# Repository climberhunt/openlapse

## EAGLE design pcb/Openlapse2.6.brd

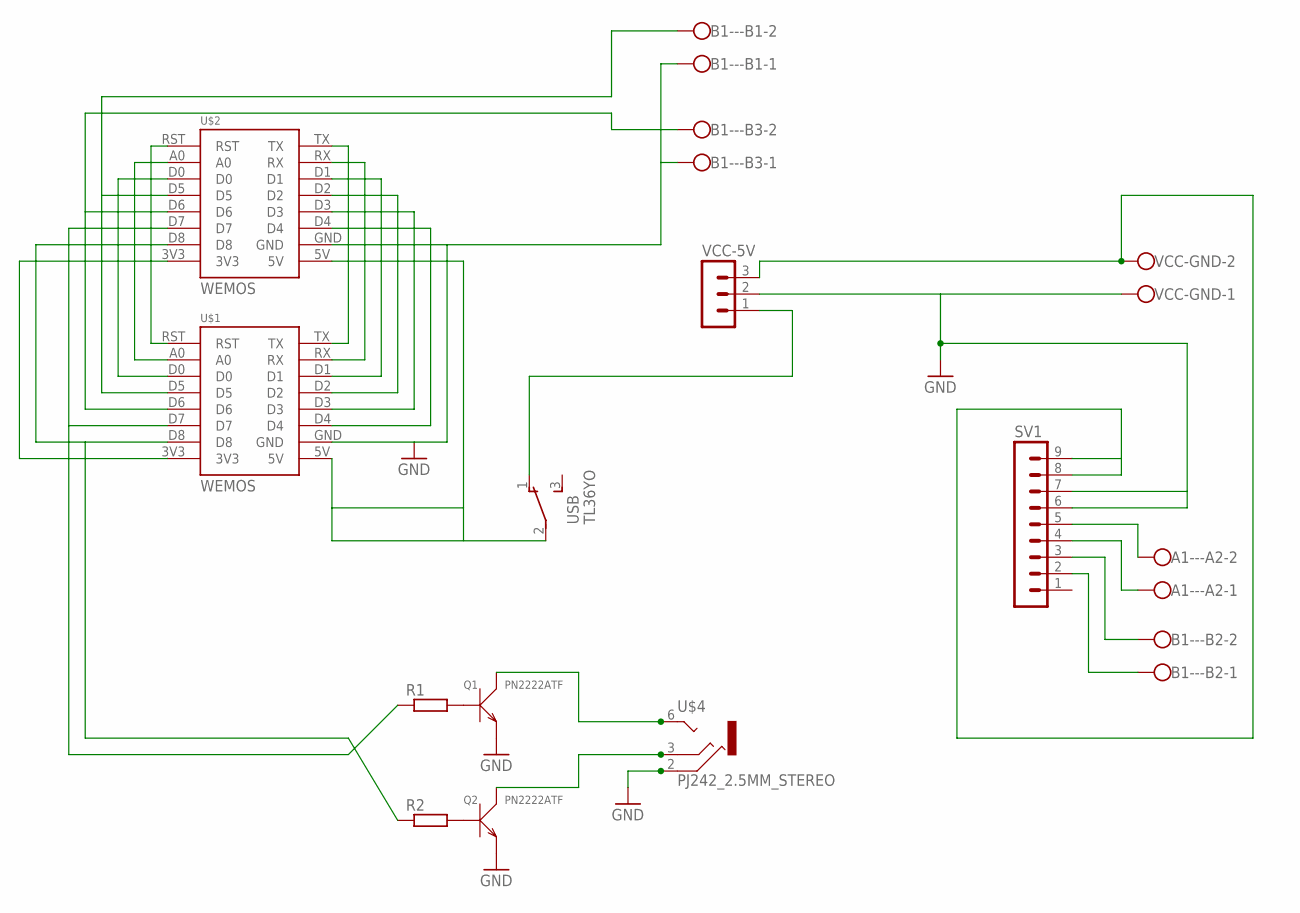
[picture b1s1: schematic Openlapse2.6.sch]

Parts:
A1---A2: W237-102
B1---B1, B1---B2, B1---B3: W237-102
Q1, Q2: PN2222ATF; TO-92
R1, R2: R0204/7; 0204/7
SV1: MA09-1
U$1, U$2: WEMOS
U$4: PJ242_2.5MM_STEREO
USB: TL36YO; TL3XYO
VCC-5V: MA03-1
VCC-GND: W237-102

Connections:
GND: B1---B1.1, B1---B3.1, Q1.1 (E), Q2.1 (E), SV1.6, SV1.7, U$1.GND, U$2.GND, U$4.2 (1), VCC-5V.2, VCC-GND.1
unnamed: SV1.8, SV1.9, VCC-5V.3, VCC-GND.2
unnamed: U$1.5V, U$2.5V, USB.2
unnamed: R2.1, U$1.D8, U$2.D8
unnamed: R1.1, U$1.D7, U$2.D7
unnamed: U$1.TX, U$2.TX
unnamed: U$1.RX, U$2.RX
unnamed: Q2.2 (B), R2.2
unnamed: Q1.2 (B), R1.2
unnamed: U$1.D1, U$2.D1
unnamed: U$1.D2, U$2.D2
unnamed: U$1.D3, U$2.D3
unnamed: U$1.D4, U$2.D4
unnamed: U$1.RST, U$2.RST
unnamed: U$1.A0, U$2.A0
unnamed: U$1.D0, U$2.D0
unnamed: B1---B1.2, U$1.D5, U$2.D5
unnamed: B1---B3.2, U$1.D6, U$2.D6
unnamed: Q1.3 (C), U$4.6 (2)
unnamed: USB.1 (O), VCC-5V.1
unnamed: U$1.3V3, U$2.3V3
unnamed: A1---A2.2, SV1.5
unnamed: A1---A2.1, SV1.4
unnamed: Q2.3 (C), U$4.3
unnamed: B1---B2.2, SV1.3
unnamed: B1---B2.1, SV1.2

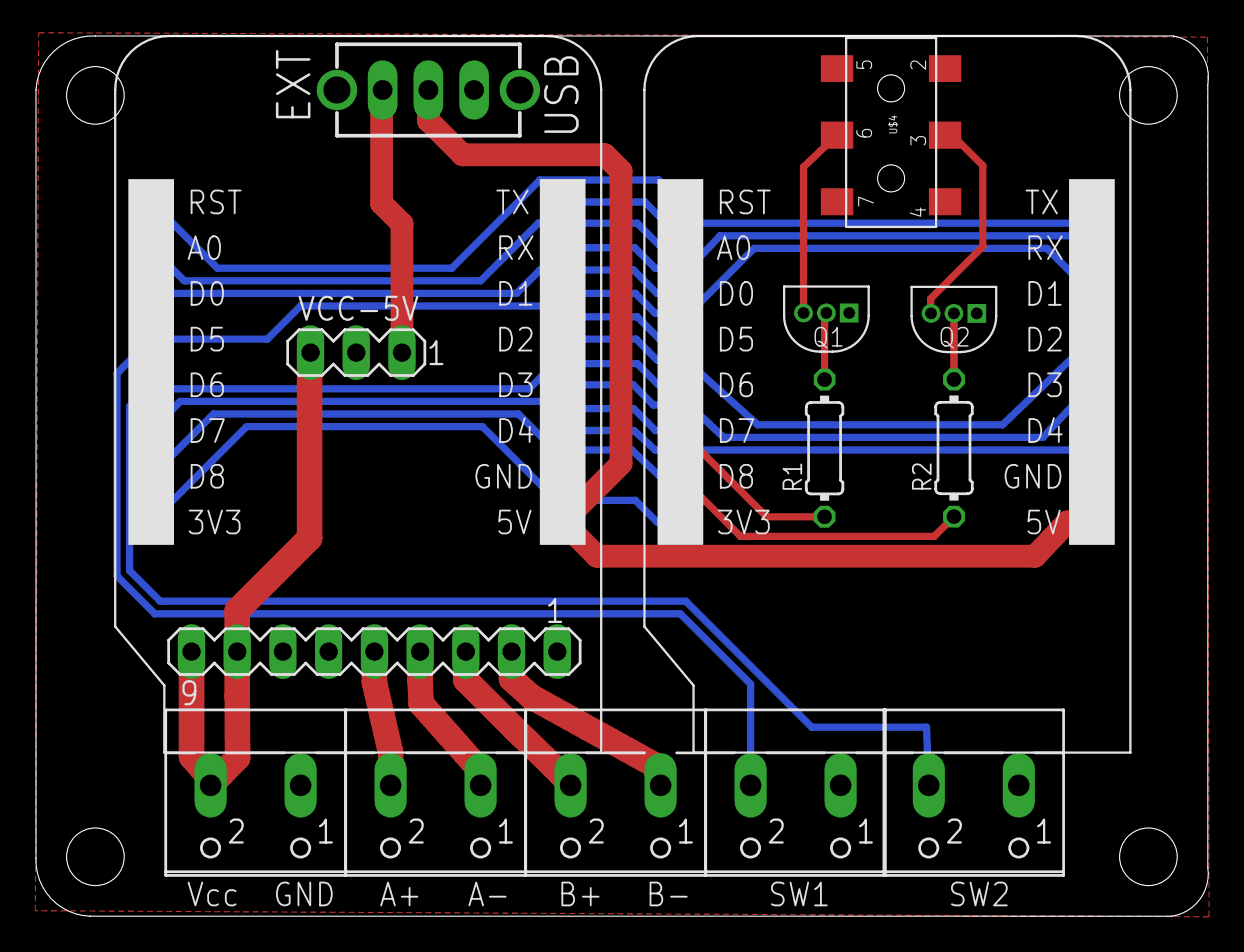
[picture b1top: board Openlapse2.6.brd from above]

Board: 2 copper layers, 65.1 x 48.9 mm, 15 parts (0 on the bottom side), 26 nets.

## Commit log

2017-06-12 Added 3D model for the 45deg bearing mount.
    This part is to allow bearings to be attached to the dolly plate so it
    can sit on the rails.
2017-06-15 add binary image for testing esptool flashing for Wemos D1 Mini
    Lots of testing still to be done on this version, but should
    function to trigger camera and move motor when used with the
    openlapse controller board.
2017-06-15 Add OpenLapse Controller Carrier Board schematics and PCB layout
    Compatible with EagleCAD
2017-06-22 add initial version of openlapse sketch
    Cut down version of the sonoff-tasmota firmware for iTead, Sonoff,
    Wemos, NodeMCU hardware by Theo Arends
    As this is a timelapse controller, it only needs a bit of a
    web interface and a way to control a motor, so all the sensor
    and MQTT code has been removed. Still a work-in-progress, but
    it you can run a timelapse, control the motor and camera (if
2017-06-22 add direction and frame counting
    Can now change direction of timelapse based on the last
    direction used in the manual motor control.
    Now counts the frames, and stops after the configured
    frame count.
2017-07-02 Complete Rail 3D model
2017-07-03 Dolly without Rail
2017-07-03 Pipe holder
2017-07-03 Updated Tube holders to 25mm available from Ali
2017-07-05 Add timing belt tensioner parts
2017-07-07 Moved over to SketchFab. Better rendering.
2017-07-07 Timing Pulley for 5mm pitch 9mm wide belt 6mm bore
2017-07-18 Fixed big in camera trigger. GPIO inverted.
2017-07-18 Added 2d parts, dolly and pipe clamp plates.
    Can be laser cut or CNC'd
2017-07-18 Add new improved timing belt clamp
2017-07-18 Added binary wiith latest bugfixes
2017-07-18 renamed mdoels directory to 3d-parts
2017-08-16 Fixed default state of shutter pin on startup
    Was defaulting to shutter active, which resulted in many
    triggers if the camera is in continuous shoot mode.
    Now comes up cleanly, no triggers.
2017-08-27 add 3D models of hoeshoe mounter controller
